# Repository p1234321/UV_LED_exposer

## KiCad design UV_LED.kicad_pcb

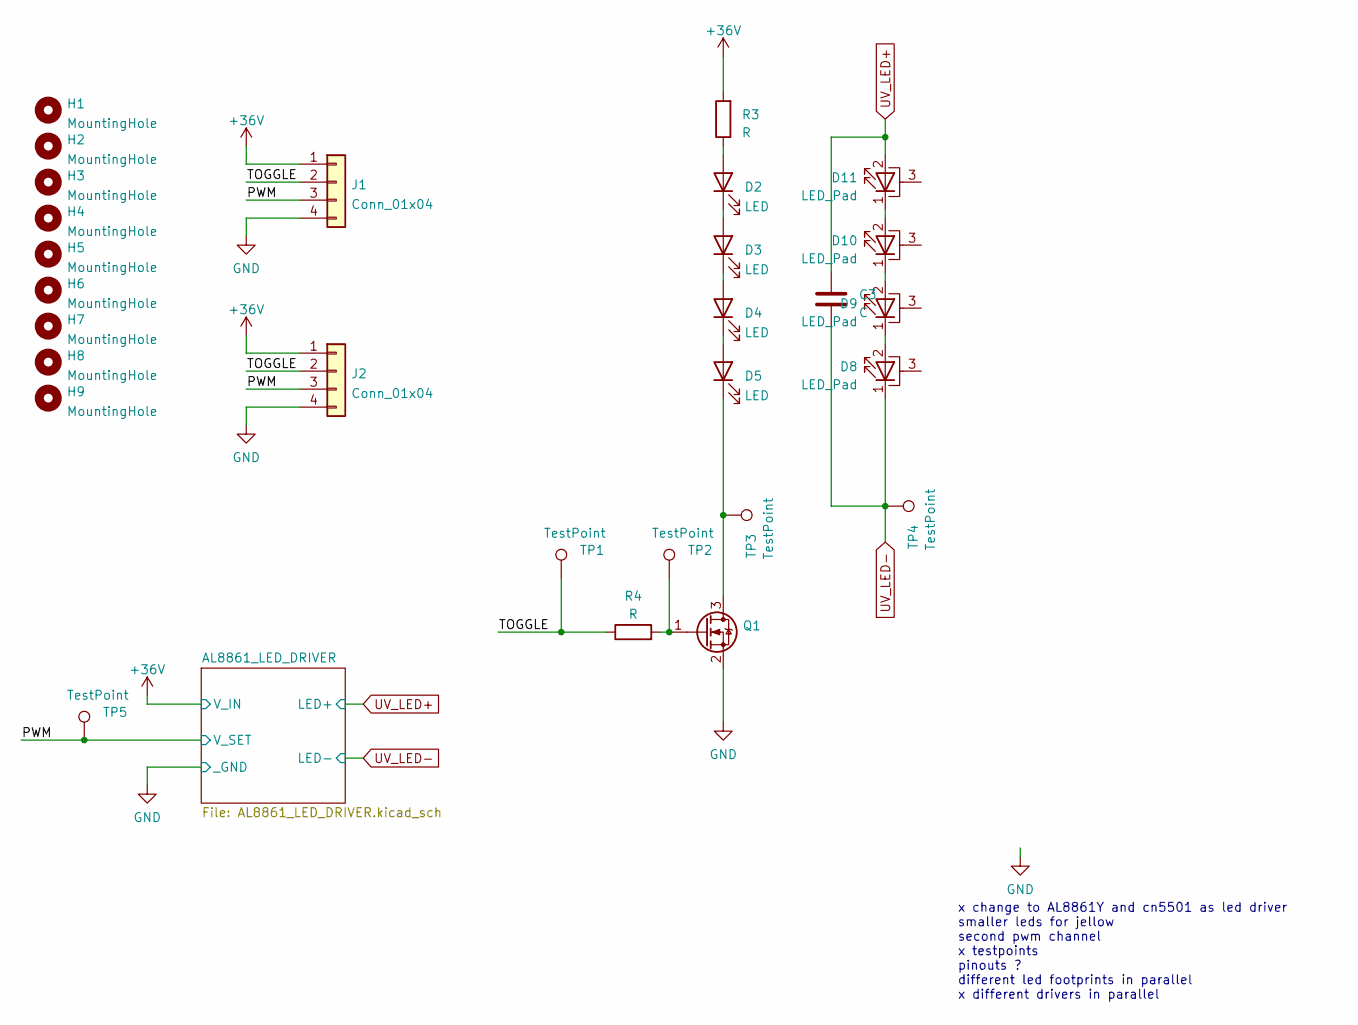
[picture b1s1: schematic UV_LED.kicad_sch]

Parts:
C3: C; C_1206_3216Metric_Pad1.33x1.80mm_HandSolder
D2, D3, D4, D5: LED; LED_1210_3225Metric_Pad1.42x2.65mm_HandSolder
D8, D9, D10, D11: LED_Pad; UV_3535
H1, H2, H3, H4, H5, H6, H7, H8, H9: MountingHole; MountingHole_3.2mm_M3
J1, J2: Conn_01x04; PinSocket_1x04_P2.54mm_Vertical
Q1: Q_NMOS_GSD; SOT-23
R3: R; R_2512_6332Metric_Pad1.40x3.35mm_HandSolder
R4: R; R_0603_1608Metric_Pad0.98x0.95mm_HandSolder
TP1, TP2, TP3, TP4, TP5: TestPoint; TestPoint_THTPad_2.0x2.0mm_Drill1.0mm

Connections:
+36V: J1.1, J2.1, R3.2; also elsewhere on the board
/PWM: J1.3, J2.3, TP5.1; also elsewhere on the board
/TOGGLE: J1.2, J2.2, R4.1, TP1.1
GND: J1.4, J2.4, Q1.2 (S); also elsewhere on the board
unnamed: D2.2 (A), R3.1
unnamed: D2.1 (K), D3.2 (A)
unnamed: D3.1 (K), D4.2 (A)
unnamed: D4.1 (K), D5.2 (A)
unnamed: D5.1 (K), Q1.3 (D), TP3.1
unnamed: D8.2 (A), D9.1 (K)
unnamed: D10.2 (A), D11.1 (K)
unnamed: D9.2 (A), D10.1 (K)
unnamed: Q1.1 (G), R4.2, TP2.1
UV_LED+: C3.1, D11.2 (A); also elsewhere on the board
UV_LED-: C3.2, D8.1 (K), TP4.1; also elsewhere on the board

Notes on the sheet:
x change to AL8861Y and cn5501 as led driver smaller leds for jellow second pwm channel x testpoints pinouts ? different led footprints in parallel x different drivers in parallel

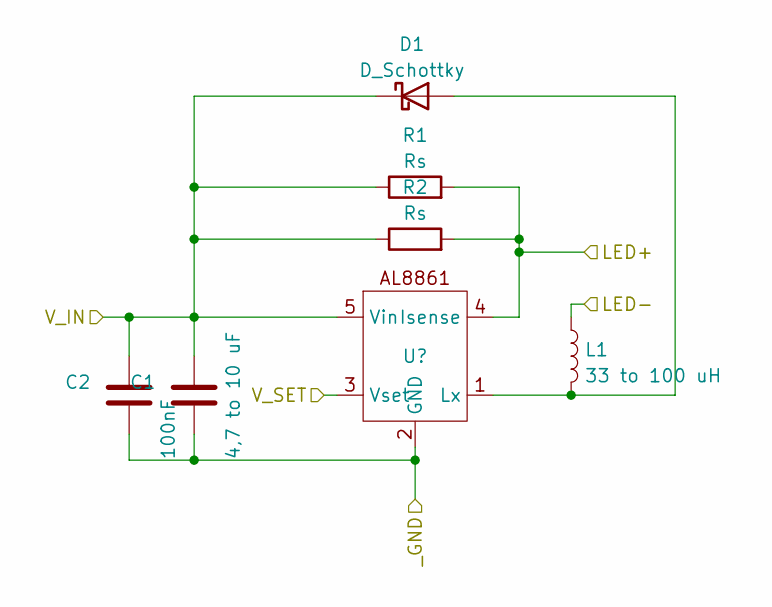
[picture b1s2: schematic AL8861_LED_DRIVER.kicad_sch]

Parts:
C1: 4,7 to 10 uF; C_1210_3225Metric_Pad1.33x2.70mm_HandSolder
C2: 100nF; C_0805_2012Metric_Pad1.18x1.45mm_HandSolder
D1: D_Schottky; D_SMA_Handsoldering
L1: 33 to 100 uH; L_12x12mm_H4.5mm
R1, R2: Rs; R_1206_3216Metric_Pad1.30x1.75mm_HandSolder
U1: SOT-89-5_Handsoldering

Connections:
+36V: C1.1, C2.1, D1.1 (K), R1.1, R2.1, U1.5 (Vin); also elsewhere on the board
/PWM: U1.3 (Vset); also elsewhere on the board
GND: C1.2, C2.2, U1.2 (GND); also elsewhere on the board
unnamed: D1.2 (A), L1.2, U1.1 (Lx)
UV_LED+: R1.2, R2.2, U1.4 (Isense); also elsewhere on the board
UV_LED-: L1.1; also elsewhere on the board

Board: 2 copper layers, 35 parts (0 on the bottom side), 16 nets, no tracks yet.

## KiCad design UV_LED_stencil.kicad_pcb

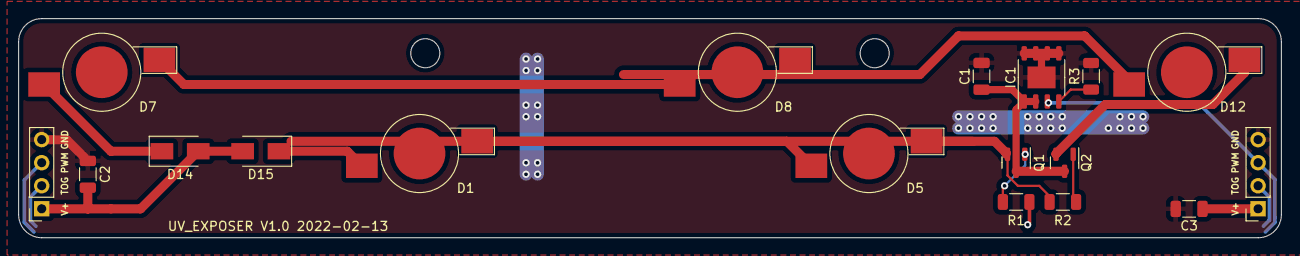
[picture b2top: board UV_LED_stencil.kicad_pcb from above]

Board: 2 copper layers, 139.1 x 24.1 mm, 20 parts (0 on the bottom side), 13 nets.

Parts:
C1: 1n 50V; C_1206_3216Metric
C2, C3: 0,1 uF 50V; C_1206_3216Metric
D1, D5, D7, D8, D12: LED; LED_1W_3W_R8
D14, D15: 1N4001; D_SMA
H5, H9: MountingHole; MountingHole_3.2mm_M3
IC1: IS31LT3178-GRLS4-TR; HSOP-8-1EP_3.9x4.9mm_P1.27mm_EP2.41x3.1mm
J1, J2: Conn_01x04; PinSocket_1x04_P2.54mm_Vertical
Q1, Q2: Q_NMOS_GDS; SOT-23
R1, R2, R3: R; R_1206_3216Metric

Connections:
+36V: C2.1, C3.1, D14.2 (A), D15.2 (A), J1.1, J2.1
/PWM: IC1.3 (EN), J1.3, J2.3
/TOGGLE: J1.2, J2.2, R1.1
GND: C1.2, C2.2, C3.2, IC1.5 (GND_1), IC1.6 (GND_2), IC1.7 (GND_3), IC1.8 (GND_4), IC1.9 (GND_5), J1.4, J2.4, R3.2
unnamed: D1.2 (A), D15.1 (K)
unnamed: D7.1 (K), D8.2 (A)
unnamed: D12.1 (K), Q2.2 (D)
unnamed: D7.2 (A), D14.1 (K)
unnamed: C1.1, IC1.1 (OUT_1), IC1.2 (OUT_2), Q1.3 (S), Q2.3 (S)
unnamed: IC1.4 (ISET), R3.1
unnamed: Q1.1 (G), R1.2
unnamed: D5.1 (K), Q1.2 (D), R2.1
unnamed: Q2.1 (G), R2.2

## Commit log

2023-12-12 .DS_Store banished!
2023-12-12 added kicad files
2023-12-12 added TX6120, CN5501 and AL8861
2023-12-12 sheet for new LED driver
2023-12-19 finalised layout
